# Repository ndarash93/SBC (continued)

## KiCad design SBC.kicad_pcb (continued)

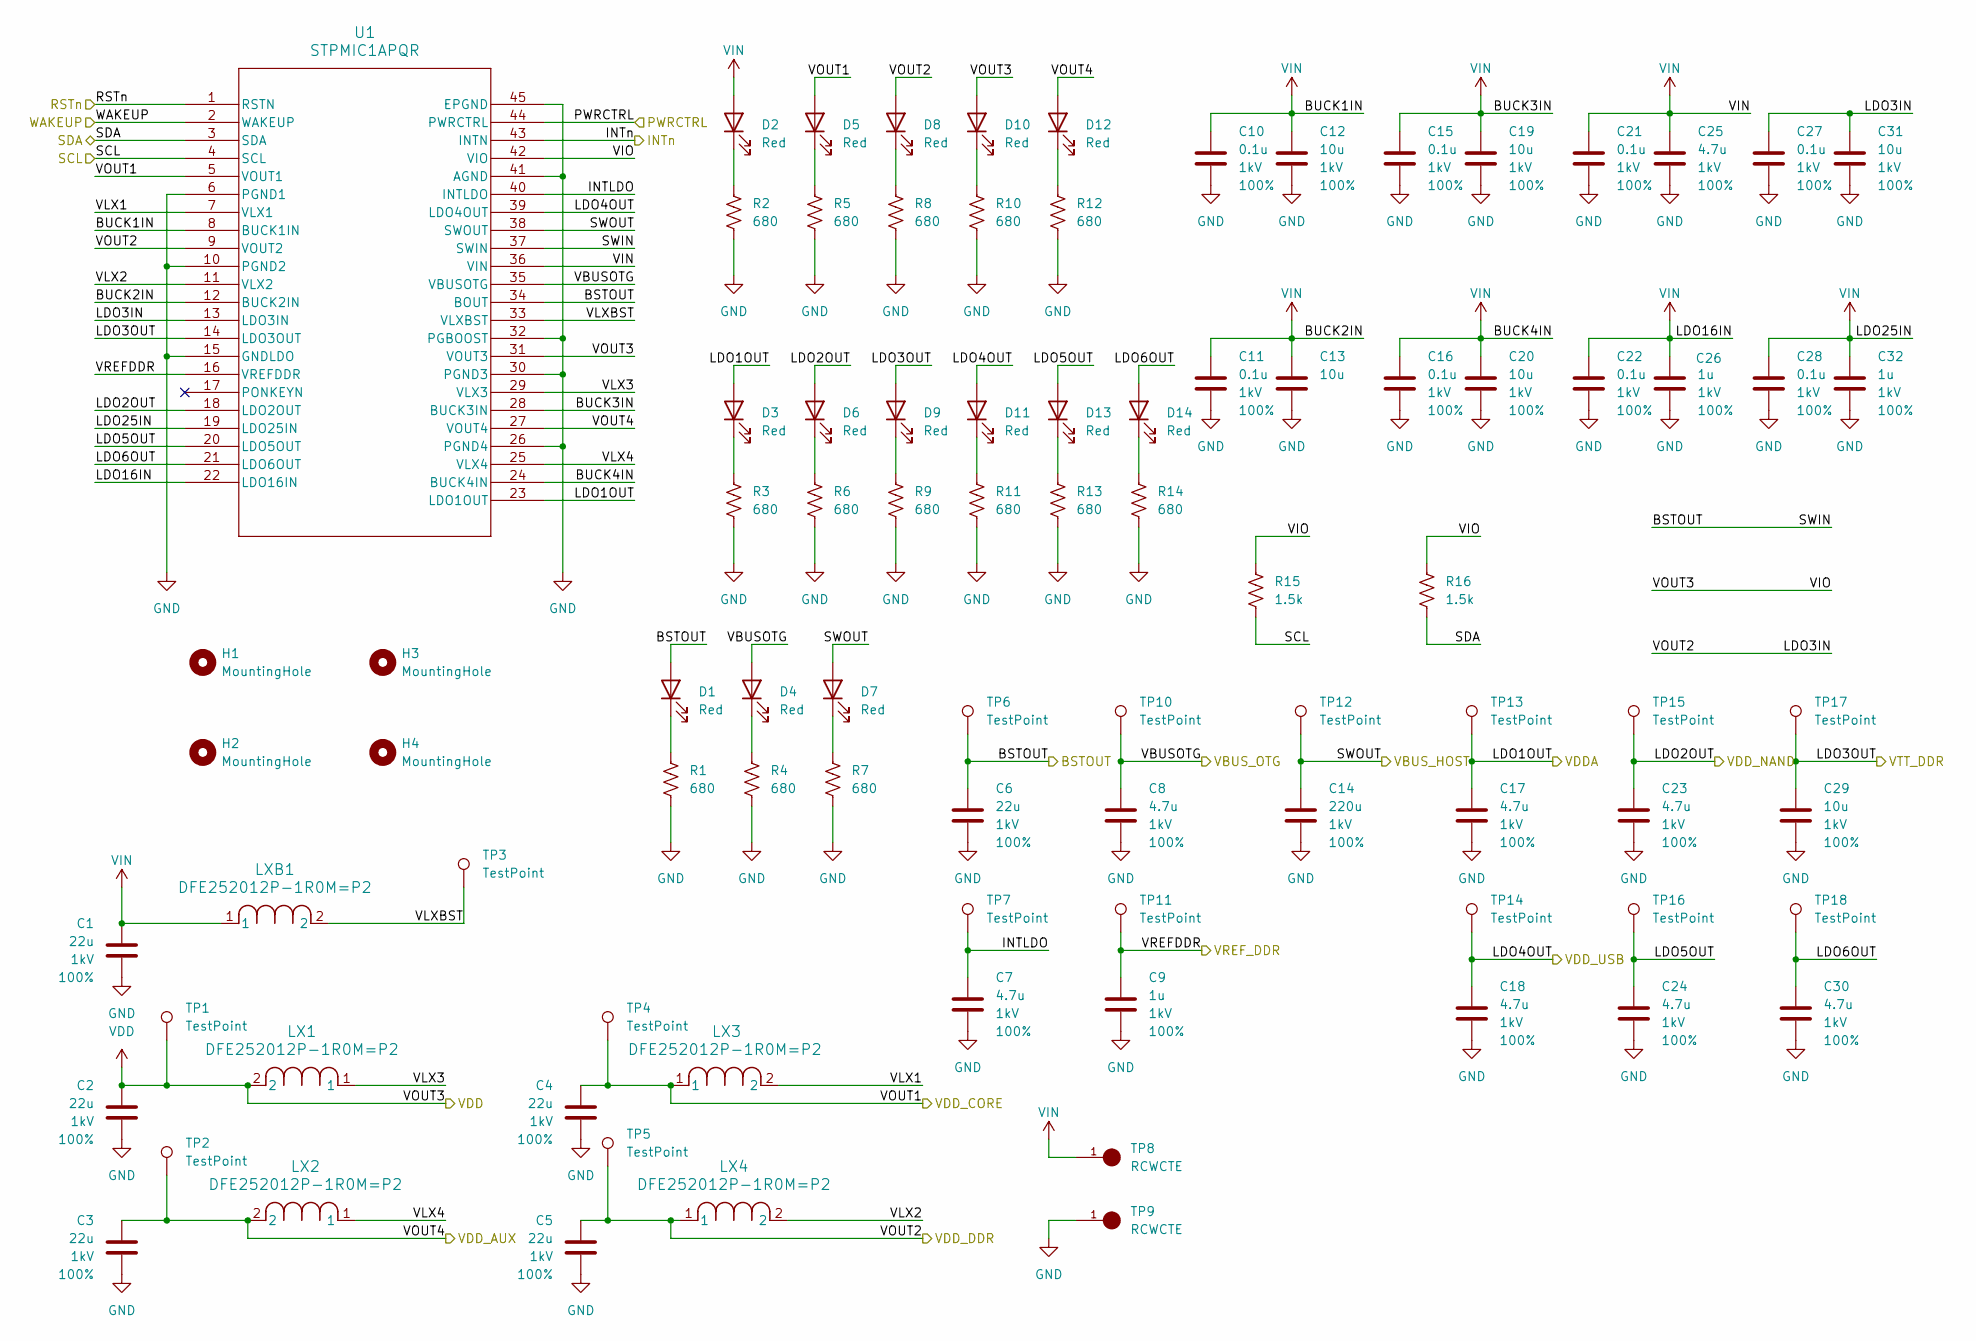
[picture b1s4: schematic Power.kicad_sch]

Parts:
C1, C2, C3, C4, C5, C6: 22u; C_0603_1608Metric; Voltage 1kV; Tolerance 100%
C7, C17, C18, C23, C24, C25, C30: 4.7u; C_0402_1005Metric; Voltage 1kV; Tolerance 100%
C8: 4.7u; C_0603_1608Metric; Voltage 1kV; Tolerance 100%
C9, C26, C32: 1u; C_0402_1005Metric; Voltage 1kV; Tolerance 100%
C10, C11, C15, C16, C21, C22, C27, C28: 0.1u; C_0402_1005Metric; Voltage 1kV; Tolerance 100%
C12, C19, C20, C29, C31: 10u; C_0603_1608Metric; Voltage 1kV; Tolerance 100%
C13: 10u; C_0603_1608Metric
C14: 220u; C_1206_3216Metric; Voltage 1kV; Tolerance 100%
D1, D2, D3, D4, D5, D6, D7, D8, D9, D10, D11, D12, D13, D14: Red; LED_0603_1608Metric
H1, H2, H3, H4: MountingHole; MountingHole_3.2mm_M3
LX1, LX2, LX3, LX4: DFE252012P-1R0M=P2; L_1008_2520Metric
LXB1: DFE252012P-1R0M=P2; L_1008_2520Metric
R1, R2, R3, R4, R5, R6, R7, R8, R9, R10, R11, R12, R13, R14: 680; R_0402_1005Metric
R15: 1.5k; R_0402_1005Metric
R16: 1.5k; LED_0402_1005Metric
TP1, TP2, TP3, TP4, TP5, TP6, TP7, TP10, TP11, TP12, TP13, TP14, TP15, TP16, TP17, TP18: TestPoint; TestPoint-0.5mm
TP8, TP9: RCWCTE; TP420X150; PARTREV 1/06/14
U1: STPMIC1APQR; WFQFN44_5X6_STM

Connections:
/MPU/DDR_VREF: C9.1, TP11.1, U1.16 (VREFDDR); also elsewhere on the board
/MPU/I2C_SCL: R15.2, U1.4 (SCL); also elsewhere on the board
/MPU/I2C_SDA: R16.2, U1.3 (SDA); also elsewhere on the board
/MPU/PWR_ON: U1.44 (PWRCTRL); also elsewhere on the board
/MPU/SDMMC2_RESET: U1.1 (RSTN); also elsewhere on the board
/MPU/VBUS_HOST: C14.1, D7.2 (A), TP12.1, U1.38 (SWOUT); also elsewhere on the board
/MPU/VBUS_OTG: C8.1, D4.2 (A), TP10.1, U1.35 (VBUSOTG); also elsewhere on the board
/MPU/VDD3V3_USB: C18.1, D11.2 (A), TP14.1, U1.39 (LDO4OUT); also elsewhere on the board
/MPU/VDDA: C17.1, D3.2 (A), TP13.1, U1.23 (LDO1OUT); also elsewhere on the board
/MPU/VDDCORE: C4.1, D5.2 (A), LX3.1, TP4.1, U1.5 (VOUT1); also elsewhere on the board
/MPU/VDD_DDR: C5.1, C27.1, C31.1, D8.2 (A), LX4.1, TP5.1, U1.9 (VOUT2), U1.13 (LDO3IN); also elsewhere on the board
/NAND/VDD: C23.1, D6.2 (A), TP15.1, U1.18 (LDO2OUT); also elsewhere on the board
/Power/BSTOUT: C6.1, D1.2 (A), TP6.1, U1.34 (BOUT), U1.37 (SWIN)
/Power/INTLDO: C7.1, TP7.1, U1.40 (INTLDO)
/Power/INTn: U1.43 (INTN)
/Power/LDO3OUT: C29.1, D9.2 (A), TP17.1, U1.14 (LDO3OUT)
/Power/LDO5OUT: C24.1, D13.2 (A), TP16.1, U1.20 (LDO5OUT)
/Power/LDO6OUT: C30.1, D14.2 (A), TP18.1, U1.21 (LDO6OUT)
/Power/VLX1: LX3.2, U1.7 (VLX1)
/Power/VLX2: LX4.2, U1.11 (VLX2)
/Power/VLX3: LX1.1, U1.29 (VLX3)
/Power/VLX4: LX2.1, U1.25 (VLX4)
/Power/VLXBST: LXB1.2, TP3.1, U1.33 (VLXBST)
/Power/VOUT4: C3.1, D12.2 (A), LX2.2, TP2.1, U1.27 (VOUT4)
/Power/WAKEUP: U1.2 (WAKEUP)
GND: C1.2, C2.2, C3.2, C4.2, C5.2, C6.2, C7.2, C8.2, C9.2, C10.2, C11.2, C12.2, C13.2, C14.2, C15.2, C16.2, C17.2, C18.2, C19.2, C20.2, C21.2, C22.2, C23.2, C24.2, C25.2, C26.2, C27.2, C28.2, C29.2, C30.2, C31.2, C32.2, R1.2, R2.2, R3.2, R4.2, R5.2, R6.2, R7.2, R8.2, R9.2, R10.2, R11.2, R12.2, R13.2, R14.2, TP9.1, U1.6 (PGND1), U1.10 (PGND2), U1.15 (GNDLDO), U1.26 (PGND4), U1.30 (PGND3), U1.32 (PGBOOST), U1.41 (AGND), U1.45 (EPGND); also elsewhere on the board
unnamed: D1.1 (K), R1.1
unnamed: D2.1 (K), R2.1
unnamed: D3.1 (K), R3.1
unnamed: D4.1 (K), R4.1
unnamed: D5.1 (K), R5.1
unnamed: D6.1 (K), R6.1
unnamed: D7.1 (K), R7.1
unnamed: D8.1 (K), R8.1
unnamed: D9.1 (K), R9.1
unnamed: D10.1 (K), R10.1
unnamed: D11.1 (K), R11.1
unnamed: D12.1 (K), R12.1
unnamed: D13.1 (K), R13.1
unnamed: D14.1 (K), R14.1
VDD: C2.1, D10.2 (A), LX1.2, R15.1, R16.1, TP1.1, U1.31 (VOUT3), U1.42 (VIO); also elsewhere on the board
VIN: C1.1, C10.1, C11.1, C12.1, C13.1, C15.1, C16.1, C19.1, C20.1, C21.1, C22.1, C25.1, C26.1, C28.1, C32.1, D2.2 (A), LXB1.1, TP8.1, U1.8 (BUCK1IN), U1.12 (BUCK2IN), U1.19 (LDO25IN), U1.22 (LDO16IN), U1.24 (BUCK4IN), U1.28 (BUCK3IN), U1.36 (VIN); also elsewhere on the board

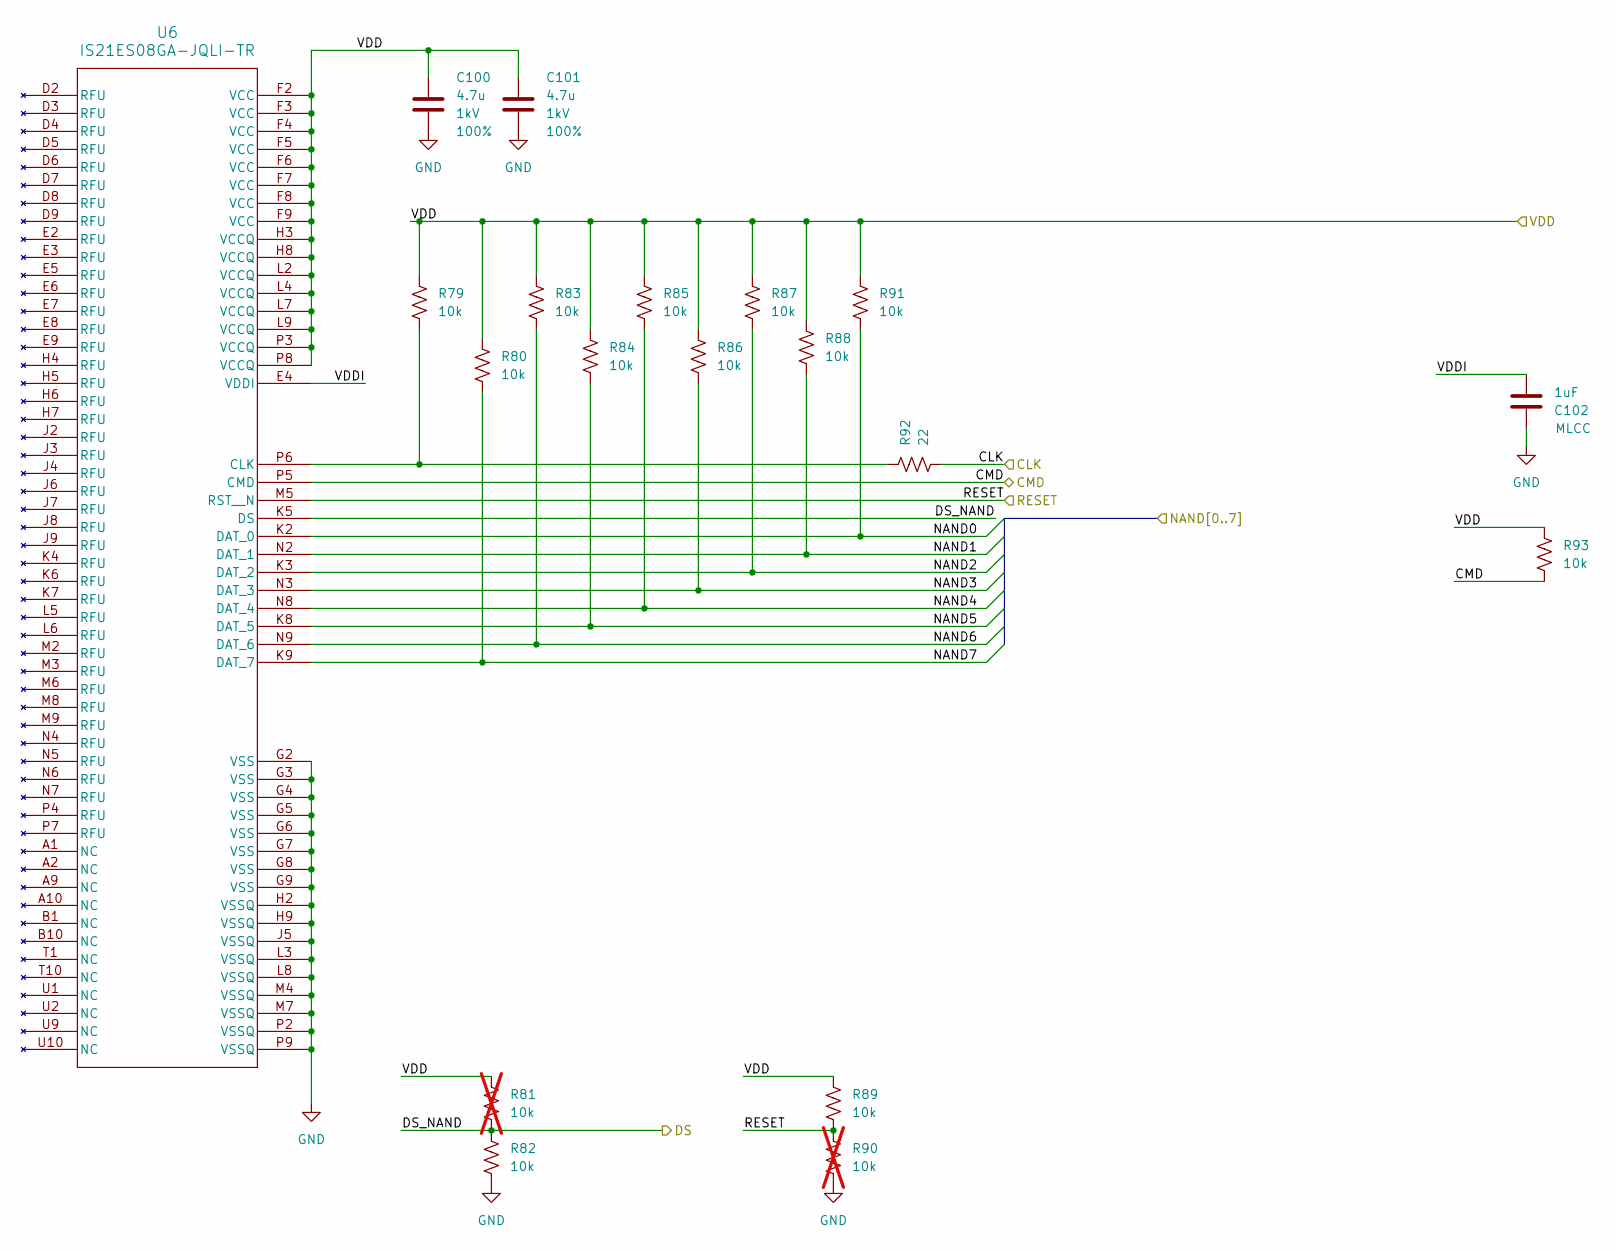
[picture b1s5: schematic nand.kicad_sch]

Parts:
C100, C101: 4.7u; C_0603_1608Metric; Voltage 1kV; Tolerance 100%
C102: 1uF; C_0402_1005Metric
R79, R80, R82, R83, R84, R85, R86, R87, R88, R89, R91, R93: 10k; R_0402_1005Metric
R81, R90: 10k; R_0402_1005Metric; not fitted
R92: 22; R_0402_1005Metric
U6: IS21ES08GA-JQLI-TR; FBGA100_ISI

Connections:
/MPU/SDMMC2_CLK: R92.2; also elsewhere on the board
/MPU/SDMMC2_CMD: R93.2, U6.P5 (CMD); also elsewhere on the board
/MPU/SDMMC2_D0: R91.2, U6.K2 (DAT_0); also elsewhere on the board
/MPU/SDMMC2_D1: R88.2, U6.N2 (DAT_1); also elsewhere on the board
/MPU/SDMMC2_D2: R87.2, U6.K3 (DAT_2); also elsewhere on the board
/MPU/SDMMC2_D3: R86.2, U6.N3 (DAT_3); also elsewhere on the board
/MPU/SDMMC2_D4: R85.2, U6.N8 (DAT_4); also elsewhere on the board
/MPU/SDMMC2_D5: R84.2, U6.K8 (DAT_5); also elsewhere on the board
/MPU/SDMMC2_D6: R83.2, U6.N9 (DAT_6); also elsewhere on the board
/MPU/SDMMC2_D7: R80.2, U6.K9 (DAT_7); also elsewhere on the board
/MPU/SDMMC2_RESET: R89.2, R90.1, U6.M5 (RST__N); also elsewhere on the board
/MPU/SDMMC2_STROBE: R81.2, R82.1, U6.K5 (DS); also elsewhere on the board
/NAND/VDD: C100.1, C101.1, R79.1, R80.1, R81.1, R83.1, R84.1, R85.1, R86.1, R87.1, R88.1, R89.1, R91.1, R93.1, U6.F2 (VCC), U6.F3 (VCC), U6.F4 (VCC), U6.F5 (VCC), U6.F6 (VCC), U6.F7 (VCC), U6.F8 (VCC), U6.F9 (VCC), U6.H3 (VCCQ), U6.H8 (VCCQ), U6.L2 (VCCQ), U6.L4 (VCCQ), U6.L7 (VCCQ), U6.L9 (VCCQ), U6.P3 (VCCQ), U6.P8 (VCCQ); also elsewhere on the board
/NAND/VDDI: C102.1, U6.E4 (VDDI)
GND: C100.2, C101.2, C102.2, R82.2, R90.2, U6.G2 (VSS), U6.G3 (VSS), U6.G4 (VSS), U6.G5 (VSS), U6.G6 (VSS), U6.G7 (VSS), U6.G8 (VSS), U6.G9 (VSS), U6.H2 (VSSQ), U6.H9 (VSSQ), U6.J5 (VSSQ), U6.L3 (VSSQ), U6.L8 (VSSQ), U6.M4 (VSSQ), U6.M7 (VSSQ), U6.P2 (VSSQ), U6.P9 (VSSQ); also elsewhere on the board
unnamed: R79.2, R92.1, U6.P6 (CLK)

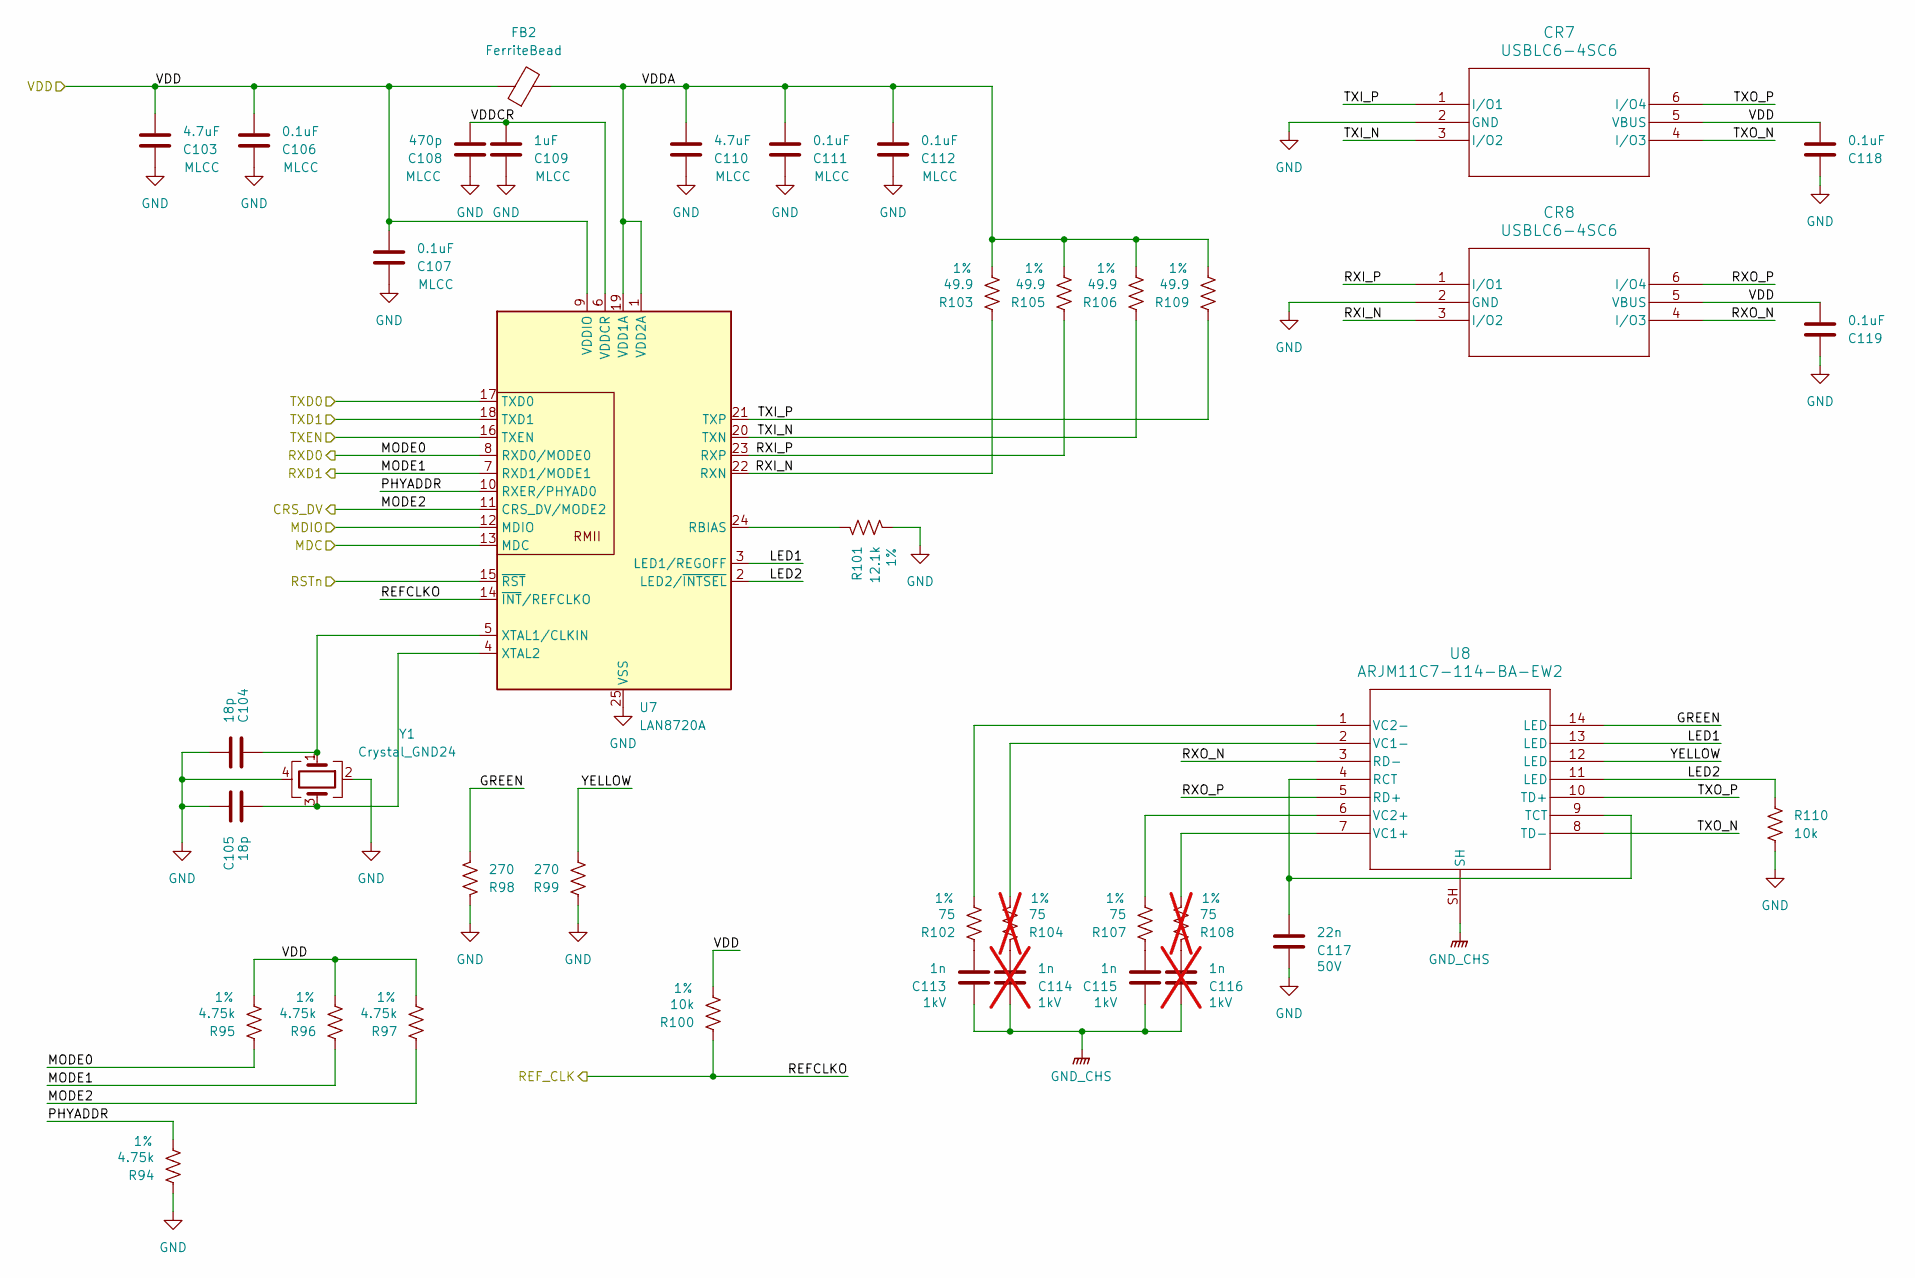
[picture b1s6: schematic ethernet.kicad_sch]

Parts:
C103, C110: 4.7uF; C_0603_1608Metric
C104, C105: 18p; C_0402_1005Metric
C106, C107, C111, C112, C118, C119: 0.1uF; C_0402_1005Metric
C108: 470p; C_0402_1005Metric
C109: 1uF; C_0402_1005Metric
C113, C115: 1n; C_0402_1005Metric; Voltage 1kV
C114, C116: 1n; C_0402_1005Metric; Voltage 1kV; not fitted
C117: 22n; C_0402_1005Metric; Voltage 50V
CR7, CR8: USBLC6-4SC6; SOT23-6L_STM
FB2: FerriteBead; L_0805_2012Metric; MPN ACML-0805-110-T
R94, R95, R96, R97: 4.75k; R_0402_1005Metric
R98, R99: 270; R_0402_1005Metric
R100, R110: 10k; R_0402_1005Metric
R101: 12.1k; R_0402_1005Metric
R102, R107: 75; R_0402_1005Metric
R103, R105, R106, R109: 49.9; R_0402_1005Metric
R104, R108: 75; R_0402_1005Metric; not fitted
U7: LAN8720A; VQFN-24-1EP_4x4mm_P0.5mm_EP2.5x2.5mm_ThermalVias
U8: ARJM11C7-114-BA-EW2; ARJM11C7-114-BA-EW2_ABR
Y1: Crystal_GND24; Crystal_SMD_Abracon_ABM8G-4Pin_3.2x2.5mm

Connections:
/Ethernet/GREEN: R98.2, U8.14 (LED)
/Ethernet/LED1: U7.3 (LED1/REGOFF), U8.13 (LED)
/Ethernet/LED2: R110.1, U7.2 (LED2/~INTSEL), U8.11 (LED)
/Ethernet/MDC: U7.13 (MDC); also elsewhere on the board
/Ethernet/MODE0: R95.1, U7.8 (RXD0/MODE0); also elsewhere on the board
/Ethernet/MODE1: R96.1, U7.7 (RXD1/MODE1); also elsewhere on the board
/Ethernet/MODE2: R97.1, U7.11 (CRS_DV/MODE2); also elsewhere on the board
/Ethernet/PHYADDR: R94.2, U7.10 (RXER/PHYAD0)
/Ethernet/REFCLKO: R100.1, U7.14 (~INT/REFCLKO); also elsewhere on the board
/Ethernet/RXI_N: CR8.3 (I/O2), R103.1, U7.22 (RXN)
/Ethernet/RXI_P: CR8.1 (I/O1), R105.1, U7.23 (RXP)
/Ethernet/RXO_N: CR8.4 (I/O3), U8.3 (RD-)
/Ethernet/RXO_P: CR8.6 (I/O4), U8.5 (RD+)
/Ethernet/TXD0: U7.17 (TXD0); also elsewhere on the board
/Ethernet/TXD1: U7.18 (TXD1); also elsewhere on the board
/Ethernet/TXEN: U7.16 (TXEN); also elsewhere on the board
/Ethernet/TXI_N: CR7.3 (I/O2), R106.1, U7.20 (TXN)
/Ethernet/TXI_P: CR7.1 (I/O1), R109.1, U7.21 (TXP)
/Ethernet/TXO_N: CR7.4 (I/O3), U8.8 (TD-)
/Ethernet/TXO_P: CR7.6 (I/O4), U8.10 (TD+)
/Ethernet/VDDA: C110.1, C111.1, C112.1, FB2.2, R103.2, R105.2, R106.2, R109.2, U7.1 (VDD2A), U7.19 (VDD1A)
/Ethernet/VDDCR: C108.1, C109.1, U7.6 (VDDCR)
/Ethernet/YELLOW: R99.2, U8.12 (LED)
/MPU/ETH1_MDIO: U7.12 (MDIO); also elsewhere on the board
/MPU/ETH_RESETn: U7.15 (~RST)
GND: C103.2, C104.2, C105.1, C106.2, C107.2, C108.2, C109.2, C110.2, C111.2, C112.2, C117.2, C118.2, C119.2, CR7.2 (GND), CR8.2 (GND), R94.1, R98.1, R99.1, R101.2, R110.2, U7.25 (VSS), Y1.2, Y1.4; also elsewhere on the board
GND_CHS: C113.2, C114.2, C115.2, C116.2, U8.SH; also elsewhere on the board
unnamed: C113.1, R102.1
unnamed: C114.1, R104.1
unnamed: C115.1, R107.1
unnamed: C116.1, R108.1
unnamed: R101.1, U7.24 (RBIAS)
unnamed: C104.1, U7.5 (XTAL1/CLKIN), Y1.1
unnamed: C105.2, U7.4 (XTAL2), Y1.3
unnamed: C117.1, U8.4 (RCT), U8.9 (TCT)
unnamed: R108.2, U8.7 (VC1+)
unnamed: R104.2, U8.2 (VC1-)
unnamed: R107.2, U8.6 (VC2+)
unnamed: R102.2, U8.1 (VC2-)
VDD: C103.1, C106.1, C107.1, C118.1, C119.1, CR7.5 (VBUS), CR8.5 (VBUS), FB2.1, R95.2, R96.2, R97.2, R100.2, U7.9 (VDDIO); also elsewhere on the board

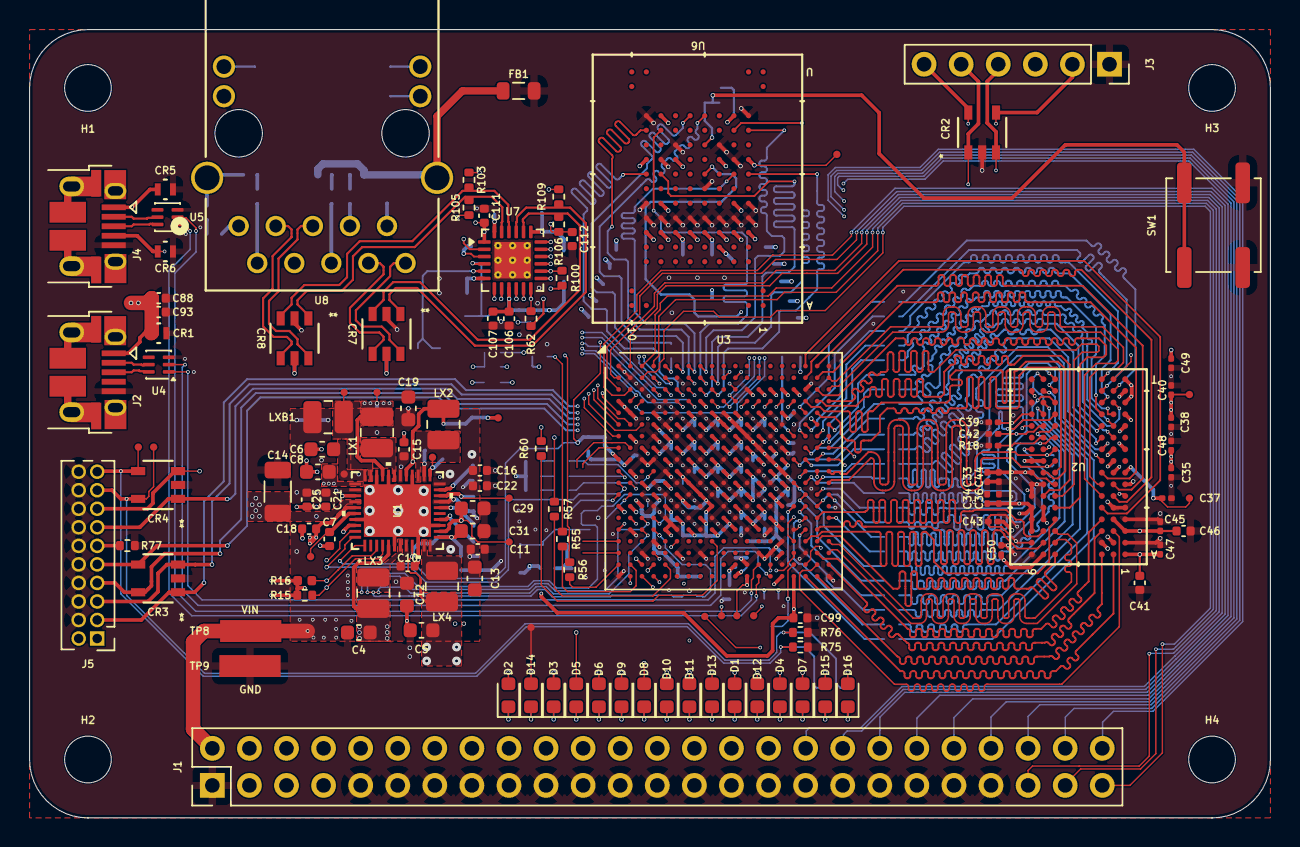
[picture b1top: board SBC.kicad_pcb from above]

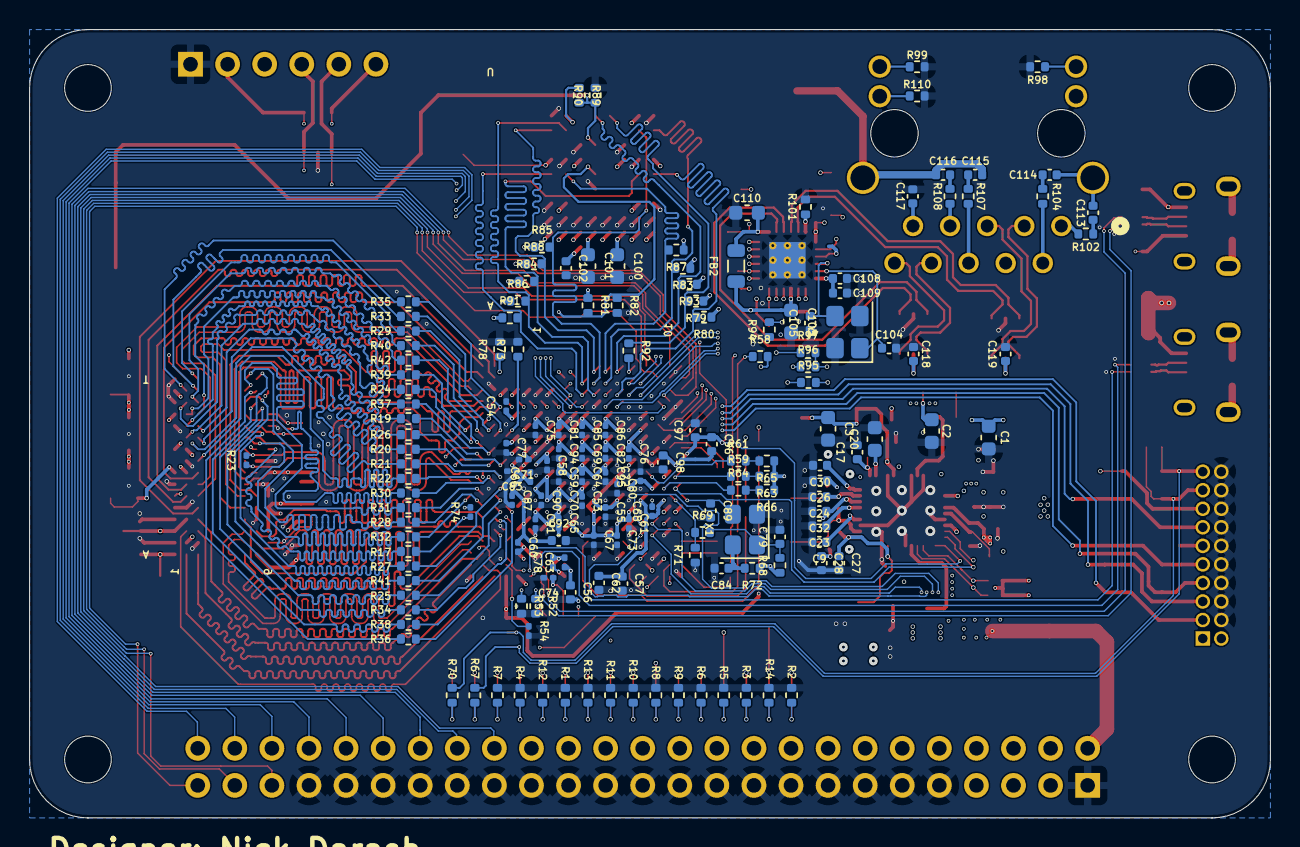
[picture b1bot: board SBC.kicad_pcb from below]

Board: 6 copper layers, 85.0 x 54.0 mm, 289 parts (161 on the bottom side), 236 nets.

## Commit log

2024-08-27 Updating ignore file
2024-08-29 Updated decoupling caps
2024-08-30 Added Power Nand USB
2024-08-31 Updating mandatory circuits
2024-09-01 adding net classes
2024-09-01 Added USB, power and other signals
2024-09-02 Working on Ethernet connections
2024-09-03 Still updating ethernet phy
2024-09-04 Moved connectors to their own sheets
2024-09-04 No changes just saving some helpful docs
2024-09-05 Finished USB JTAG connectors and cleaned up schematic
2024-09-06 Adding more decoupling and started on DSI connector
2024-09-07 Adding another usb and cleanup
2024-09-14 Selecting footprints
2024-09-15 Added all footprints and kicked off pcb design
2024-09-16 Layout started
2024-09-17 Component placement
2024-09-17 Roughly placed all components
2024-09-19 Added notes
2024-09-20 Added some routing, updated constraints and added net classes
2024-09-20 minor changes
2024-09-22 Routed PMIC and started on MPU
2024-09-22 Routing DDR
2024-09-23 I am not good at routing
2024-09-24 DDR is hard
2024-09-25 DDR routing forever
2024-09-26 redoing ddr routing
2024-09-27 DDR routing continued
2024-09-27 DDR routing first pass complete
2024-09-28 Progress on DDR routing
2024-09-28 No changes
2024-09-29 Routing routing routing
2024-09-29 added some vias
2024-09-30 eMMC routing done
2024-10-01 More routing
2024-10-03 Ethernet routing
2024-10-05 Routing
2024-10-06 Routed some of the GPIO
2024-10-07 Routing GPIOs
2024-10-08 Rerouting all the spare pins
2024-10-09 Routing of GPIOs
2024-10-10 Routed JTAG
2024-10-12 Routed GPIOs
2024-10-14 Added decoupling back in and changed to 0201
2024-10-16 Fixing some stuff
2024-10-17 Incremental changes
2024-10-18 Everything is placed
2024-10-19 Initial routing complete
2024-10-21 Finished routing and added LP_PWR connection
2024-10-23 Cleaning up routing and fixing DRC errors
2024-10-23 Fixed
2024-10-24 Fixing DRC errors
2024-10-28 Fixing DRC
2024-10-30 Fixed EMMC DRC errors
2024-10-31 Fixed DRC errors and updated DDR trace widths
2024-11-03 Adding return current vias and stiching
2024-11-03 Need to redo all the DDR routing again
2024-11-03 Added documentation showing DDR layout requirements
2024-11-06 progress
2024-11-08 DDR Routing...
2024-11-10 DDR added switch backs
2024-11-12 DDR added switch backs cont
2024-11-14 More DDR Routing
2024-11-24 DRC Error Checking
2024-11-24 Updating USB routing
2024-11-24 Added text
2024-11-25 Completed error checking
2025-10-15 Fixing some spacing issues
2025-10-15 Added in new MPU
2025-10-15 Schemtic work to add in new MPU
2025-10-16 Updating VDD_USB
2025-10-16 Updating schematic
2025-10-17 Updated memory added 33ohm resistors
2025-10-18 Started an entire reroute
2025-10-19 DDR Routing commenced
2025-10-20 DDR routing
2025-10-21 DDR complete needs polish
2025-10-24 DDR Routing more
2025-10-25 DDR done for now
2025-10-26 Layers were toggled
2025-10-26 PMIC Routing
2025-10-27 Routing PMIC
2025-10-27 Routing Power
2025-10-28 Power routing
2025-10-30 Finished DDR power and fixed a number of violations
2025-10-30 Update DDR and started EMMC
2025-10-31 Routing eMMC
2025-11-02 Routing ethernet
2025-11-03 eMMC routing
2025-11-04 Eth Routing
2025-11-08 Routing Eth
2025-11-09 Routed UART4 and OSC
2025-11-11 Routing power and fixing minor things
2025-11-12 Cleaning up routing
2025-11-13 Finished main routing
2025-11-15 Fixing errors
2025-11-28 Trying to understand the series resitors on DDR routing
2025-11-30 Adding GPIOs
2025-12-06 Still adding GPIO pinout
2025-12-07 Finished routing GPIOs
2025-12-15 Ran some basic sims
2026-01-27 Claude helped create a DFM checker for JLC
2026-03-15 No change
2026-03-16 Fixed skew on A6
2026-03-20 Moving Silk Screen around
2026-03-24 Organizing REFDES
